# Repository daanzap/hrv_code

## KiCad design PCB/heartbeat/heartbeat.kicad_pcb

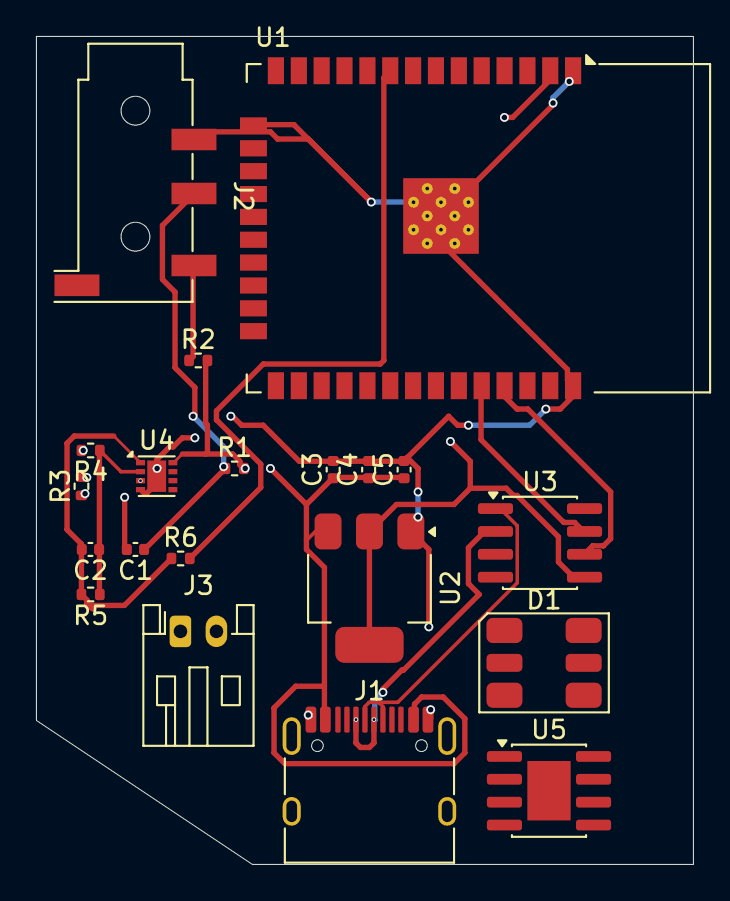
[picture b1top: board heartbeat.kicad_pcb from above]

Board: 4 copper layers, 36.5 x 46.0 mm, 20 parts (0 on the bottom side), 13 nets.

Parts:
C1, C2, C3, C4, C5: C_Small; C_0402_1005Metric
D1: Inolux_IN-P55TATRGB; LED_Inolux_IN-P55TATRGB_PLCC6_5.0x5.5mm_P1.8mm
J1: USB_C_Receptacle; USB_C_Receptacle_HRO_TYPE-C-31-M-12
J2: AudioJack3; Jack_3.5mm_KoreanHropartsElec_PJ-320D-4A_Horizontal
J3: Conn_01x02; JST_PH_S2B-PH-K_1x02_P2.00mm_Horizontal
R1, R2, R3, R4, R5, R6: R_Small; R_0402_1005Metric
U1: ESP32-WROOM-32
U2: AMS1117-3.3; SOT-223-3_TabPin2
U3: CH330N; SOIC-8_3.9x4.9mm_P1.27mm
U4: LM358_DFN; DFN-8-1EP_2x2mm_P0.5mm_EP1.05x1.75mm
U5: LGS5500EP; SOIC-8-1EP_3.9x4.9mm_P1.27mm_EP2.41x3.3mm

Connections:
/3V3: U1.2 (VDD), U2.2 (VO), U3.5 (VCC)
/5V: C3.1, C4.1, C5.1, J1.A4 (VBUS), J1.A9 (VBUS), J1.B4 (VBUS), J1.B9 (VBUS), R1.2, R2.2, U2.3 (VI), U4.8 (V+), U5.2 (VIN_2)
/hb_signal: R6.2, U1.9 (IO33)
/rx: U1.34 (RXD0/IO3), U3.7 (RXD)
/tx: U1.35 (TXD0/IO1), U3.6 (TXD)
GND: C3.2, C4.2, C5.2, J1.A1 (GND), J1.A12 (GND), J1.B1 (GND), J1.B12 (GND), J2.S, R3.1, R4.2, U1.1 (GND), U1.15 (GND), U1.38 (GND), U1.39 (GND), U2.1 (GND), U4.4 (V-), U4.9 (PAD)
unnamed: C1.1, R1.1
unnamed: C2.2, R5.2, R6.1, U4.1
unnamed: J2.T, R2.1
unnamed: J1.A6 (D+), J1.B6 (D+), U3.1 (UD+)
unnamed: J1.A7 (D-), J1.B7 (D-), U3.2 (UD-)
unnamed: C1.2, R3.2, U4.3 (+)
unnamed: C2.1, R4.1, R5.1, U4.2 (-)

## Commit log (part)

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2026-06-10 added files
